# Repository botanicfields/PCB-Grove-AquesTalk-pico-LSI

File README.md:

# PCB-Grove-AquesTalk-pico-LSI
# AquesTalk pico LSI用Grove(M5)接続基板
AquesTalk pico LSI into the Grove of M5

# 1. 概要
　「AquesTalk pico LSI用Grove(M5)接続基板」は、市販の音声合成専用LSI「AquesTalk pico LSI」（別売）をGroveコネクタでM5シリーズに接続するための基板です。  
　AquesTalk pico LSIの詳細は、データシートを参照ください。
- [Data Sheet: 音声合成 LSI 「AquesTalk pico LSI」ATP3011](https://www.a-quest.com/archive/manual/atp3011_datasheet.pdf)
- [Data Sheet: 音声合成 LSI 「AquesTalk pico LSI」ATP3012](https://www.a-quest.com/archive/manual/atp3012_datasheet.pdf)

### 基板V03 の変更点
　2022年10月から基板V03を提供しています。ピンソケットJ7を追加しました。

### 委託販売
（スイッチサイエンス扱い）[AquesTalk pico LSI用Grove(M5)接続基板](https://www.switch-science.com/catalog/7625/)

### 動作例
- (YouTube）[AquesTalk pico LSI into the Grove of M5](https://youtu.be/mju6NteZsHU)  
M5AtomにI2Cで接続しています。以下のサンプルプログラムを使用しています。  
[GitHub: botanicfields/PCB-Grove-AquesTalk-pico-LSI/tree/main/BF-035_Wire](https://github.com/botanicfields/PCB-Grove-AquesTalk-pico-LSI/tree/main/BF-035_Wire)
- (YouTube）[般若心経 by AquesTalk pico LSI and M5Stack, Glove PCB, I2C](https://youtu.be/BDH4y0ca8p8)  
M5SrackにI2Cで接続しています。基板V03のJ7とM5StackのGPIO35をジャンパワイヤーで接続しています。以下のサンプルプログラムを使用しています。  
[GitHub: botanicfields/PCB-MBUS-AquesTalk-pico-LSI/tree/main/BF-034_han-nya](https://github.com/botanicfields/PCB-MBUS-AquesTalk-pico-LSI/tree/main/BF-034_han-nya)

### 組み立て例
　AquesTalk piso LSI（28ピンDIPタイプ）1個をICソケットに装着します。ATP3011用とATP3012用のソケットがあります。どちらか一方のみを装着してください。  
AquestTalk pico LSIの取り付け: 左 ATP3011, 右 ATP3012  

## 1.1 特徴
- AquesTalk pico LSI（28ピンDIPタイプ）1個を搭載できます。
- ATP3011, ATP3012の両方に対応しています。
- パワーアンプ（LM4871）を内蔵し、スピーカーを直接駆動できます。
- M5シリーズのGrove仕様に合わせ、電源+5V、信号3.3Vに対応します。
- AquestTalk pico LSIは3.3Vで動作し、M5シリーズに直結できます。
- DIPスイッチで動作モード・通信モードを設定できます。
- 動作モード・通信モードの変更を反映するリセットボタンがあります。
- I2C接続用、UART接続用のGroveコネクタがあり、接続方法を選べます。
- スタンドアロンモードのためのコネクタがあります。
- SPI接続も可能です（ハンダ付けが必要です）。

DIP: Dual In-line Package  
I2C: Inte-Integrated Circuit  
UART: Universal Asynchronous Receiver Transmitter  
SPI: Serial Peripheral Interface

## 1.2 内容物
- AquesTalk pico LSI用Grove(M5)接続基板（完成品）1枚  
- Groveケーブル20cm 1本（M5Stack純正品）  
- 説明書 1部  

※ AquesTalk pico LSIは付属しません。  
※ スピーカー、スピーカーケーブルは付属しません。  
※ ケースや足などは付属しません。

### 商品写真（基板V03）
写真: 内容物、基板裏面  

## 1.3 別途必要なもの
- AquesTalk pico LSI（秋月電子通商扱い）  
[音声合成ＬＳＩ　ＡＴＰ３０１１Ｆ１－ＰＵ（ゆっくりな女性の音声）
ATP3011F1-PU](https://akizukidenshi.com/catalog/g/gI-06220/)  
[音声合成ＬＳＩ　ＡＴＰ３０１１Ｆ４－ＰＵ（かわいい女性の音声）
ATP3011F4-PU](https://akizukidenshi.com/catalog/g/gI-05665/)  
[音声合成ＬＳＩ　ＡＴＰ３０１１Ｍ６－ＰＵ（男性の音声）
ATP3011M6-PU](https://akizukidenshi.com/catalog/g/gI-06225/)  
[音声合成ＬＳＩ　ＡＴＰ３０１２Ｆ６－ＰＵ（女性の音声明瞭版）
ATP3012F6-PU](https://akizukidenshi.com/catalog/g/gI-09973/)  
[音声合成ＬＳＩ　ＡＴＰ３０１２Ｒ５－ＰＵ（小型ロボットの音声）
ATP3012R5-PU](https://akizukidenshi.com/catalog/g/gI-11517/)  
- スピーカー、スピーカーケーブル  
4～8Ω程度、1W以上が望ましいです
- 工具  
ドライバ（ターミナルブロックの締め付けに必要です）など
- M5Stack, M5Atom  
サンプルプログラムは、M5Stack Core Basic, M5Atomで動作を確認しています
- Arduino-IDEが動作する環境  
サンプルプログラムは、Arduino IDE用です
- その他  
SLEEP信号などを接続する場合には、ジャンパワイヤー等が必要です。SPI接続の場合には、ピンヘッダおよびハンダ付けが必要です

# 2. 接続

## 2.1 I2C接続
　SCL, SDAの表記のあるGroveコネクタJ5に接続します。基板上にプルアップ抵抗はありません。M5シリーズ側でのプルアップを使用します。

### (1)M5AtomのGroveコネクタに接続  
　I2Cとして、SCL=GPIO32, SDA=GPIO26を指定します。サンプルプログラムではWire1を選択します。

### (2)「M5Atom用GROVEコネクタ基板※（別売）」経由で接続  
　I2Cとして、デフォルトのWire（SCL=GPIO21, SDA=GPIO25）を使用できます。  
※（スイッチサイエンス扱い）[M5Atom用GROVEコネクタ基板](https://www.switch-science.com/catalog/7309/)

### (3)M5StackのGroveコネクタに接続  
　I2Cとして、デフォルトのWire（SCL=GPIO22, SDA=GPIO21）を使用できます。

## 2.2 UART接続
　TX, RXの表記のあるGroveコネクタJ4に接続します。基板上のTXがM5シリーズのRXに、基板上のRXがM5シリーズのTXに接続されます。

### (1)M5AtomのGroveコネクタに接続  
　M5Atom側は、RX=GPIO32, TX=GPIO26を指定します。

### (2)M5StackのGPIOに接続  
　接続には、「GROVE - 4ピン - ジャンパオスケーブル※（別売）」相当のケーブルが必要です。M5Stack側は、RX=GPIO16, TX=GPIO17, +5V, GND を接続します。  
※（スイッチサイエンス扱い）[GROVE - 4ピン - ジャンパオスケーブル](https://www.switch-science.com/catalog/6245/)

## 2.3 SPI接続
　SS, +5V, GNDは、ピンソケットJ3に接続します。SCK, MOSI, MISOは、J1(ICSP)に接続します。ICSPのピンヘッダは実装していません。ピンヘッダを別途手配いただき、基板へハンダ付けしてください。接続にはジャンパワイヤー等が必要です。
- SPI: Serial Periphral Interface
- SCK: Serial ClocK
- MOSI: Master Out Slave In
- MISO: Master In Slave Out
- SS: Slave Select
- GND: Ground
- ICSP: In Circuit Serial Programming

### M5StackのGPIOに接続
　接続にはジャンパワイヤー等が必要です。SCK=GPIO18, MISO=GPIO19, MOSI=GPIO23, SS=GPIO5, +5V, GND を接続します。

## 2.4 スタンドアロン
　J2に「ダイオードマトリクススイッチ16基板※」を接続し、ボタン操作で15種類の音声を再生できます。以下の写真でM5Stackは、電源として使用しています。  
※（スイッチサイエンス扱い）[ダイオードマトリクススイッチ16基板](https://www.switch-science.com/catalog/7626/)

## 2.5 その他共通
### J3 SLEEP信号
　AquesTalk pico LSIのSLEEPピンをGPIOに接続できます。SLEEP=LowでAquesTalk pico LSIがスリープ状態になります。ATP3011のUART接続において9600bpsより速い速度が必要な場合、「セーフモード」ではなく「コマンド入力モード」が必要であり、速度設定のためにSLEEPの接続が必要です。

### J3 PLAY信号
　AquesTalk pico LSIのPLAYピンをGPIOに接続できます。AquesTalk pico LSIが音声再生中の間、PLAY=Lowとなります。

### J6 スピーカー
　スピーカーを接続します。2本のいずれもGNDではありません。

### J7 音声信号（基板V03）
　音量調節ボリュームに入る時点のアナログ音声をジャンパワイヤー等に取り出すことができます。ATP3011、ATP3012でピンが異なります。  
ATP3011の例  
  
ATP3012の例  

# 3. 設定（DIPスイッチ）
　動作モードおよび使用するインタフェース（通信モード）に合わせて、基板上のDIPスイッチを設定します。おすすめはI2C接続です。DIPスイッチの設定はリセット時に反映されます。**DIPスイッチの設定を変更後、基板上のリセットボタンを押す必要があります**。出荷時の設定は、セーフモード・I2C接続・パワーアンプが常に動作状態（OFF,ON,OFF,ON,ON）です。

| 1 | 2 | 3 | 4 | 5 |動作モード|通信モード|備考|
|:-:|:-:|:-:|:-:|:-:|:-:|:-:|:- |
|OFF|OFF|OFF|ON | - | コマンド入力モード |I2C |I2CアドレスはEEPROMに設定した値（初期値0x2E）|
|OFF|ON |OFF|ON | - | セーフモード |I2C |I2Cアドレスは強制的に0x2E|
|OFF|OFF|OFF|OFF| - | コマンド入力モード |UART|設定されたスピードで動作 (*1) |
|OFF|ON |OFF|OFF| - | セーフモード |UART|強制的に9600bpsで動作|
|OFF| - |ON |OFF| - | - | SPI mode 3 | - |
|OFF| - |ON |ON | - | - | SPI mode 0 |サンプルプログラムはSPI mode 0で動作|
|ON |OFF| - | - | - | スタンドアロンモード | - |PC0-3の信号入力によりプリセットメッセージを選択して再生|
|ON |ON | - | - | - | デモモード | - |プリセットメッセージを順番に自動再生|
| - | - | - | - |ON | - | - |パワーアンプが常に動作状態 |
| - | - | - | - |OFF| - | - |音声再生中以外は、パワーアンプをシャットダウンする(*2)|

※ 1, 2, 3, 4, 5は、DIPスイッチの番号です。DIPスイッチはONでGND接続のため、ON=0, OFF=1です。  
(*1) ATP3011の場合、SLEEP解除後の'?'送信で自動設定します。ATP3012の場合EEPROMに設定します。  
(*2) 音声再生の前後にノイズが発生します。

# 4. サンプルプログラム
　AquesTalk pico LSIをM5StackまたはM5Atomに接続し、I2C(Wire), UART(Serial), SPIで動作させるプログラムです。デモの内容は同じです。Arduino-IDE環境で使用します。基板の接続や設定を予め使用するインタフェースに合わせておく必要があります。

### BF-035_Wireフォルダ
　AqeusTalk pico LSIをI2Cで動作させるサンプルプログラムです。#defineでM5Stack, M5Atomのいずれかを選択します。

### BF-035_Serialフォルダ
　AqeusTalk pico LSIをUARTで動作させるサンプルプログラムです。#defineでM5Stack, M5Atomのいずれかを選択します。

### BF-035_Spiフォルダ
　AqeusTalk pico LSIを SPIで動作させるサンプルプログラムです。M5Stack専用です。

## 4.1 ボタン操作 .. loop()
　ボタンを押すと、ソースコードのpreset_msgを発声します。初期値はpreset_msg[0]です。

| M5 | ボタン | 停止中 | 発声中 |
|:-:|:-:|:-:|:-:|
|M5Stack| A   | 1つ前のpreset_msgを発声 | 発声を中断して1つ前のpreset_msgを発声 |
|M5Stack| B   | 現在のpreset_msgを発声 | 発声を中断して停止 |
|M5Stack| C   | 1つ後のpreset_msgから連続して発声 | 発声を中断して1つ後のpreset_msgから連続して発生 |
|M5Atom | Btn | 現在のpreset_msgから連続して発声 | 発声を中断して停止 |

## 4.2 setup()
- SLEEPピンをHighにする（デフォルト: 実行しない）  
　AquesTalk pico LSIのSLEEPピンとが接続したGPIO5をHIGHにしてSLEEPでない状態にします。

- UARTスピードを設定（ATP3011が対象。UARTのみ。デフォルト: 実行しない）  
　AquesTalk pico LSI (ATP3011) のUARTスピードを設定します。GPIO5がAquesTalk pico LSIのSLEEPピンと接続している必要があります。

- UARTスピードを書き換え（ATP3012が対象。UARTのみ。デフォルト: 実行しない）  
　AquesTalk pico LSI (ATP3012) のUARTスピードを書き換えます。

- I2Cアドレスを書き換え（I2Cのみ。デフォルト: 実行しない）  
　AquesTalk pico LSIのI2Cアドレスを書き換えます。

- プリセットメッセージを書き込む（デフォルト: 実行しない）  
　AquesTalk pico LSIにプリセットメッセージとして、ソースコード内のpreset_msgデータを書き込みます。時間がかかります。

- EEPROMデータをダンプ（デフォルト: 実行しない）  
　AquesTalk pico LSIのEEPROMデータをシリアルモニタに表示します。時間がかかります。

- AquesTalk pico LSIのバージョンをシリアルモニタに表示

- チャイムJを発声

- チャイムKを発声

# 5. ライブラリ
　AquesTalk pico LSIを使用するためのライブラリです。

## 5.1 BF_AquesTalkPico.h
　I2C, UART, SPI共通の基本クラスです。接続するインタフェースに依ってI2C(Wire), UART(Serial), SPIのいずれかの派生クラスを使用する必要があります。

### (1) virtual int Send(const char* msg) = 0
　AquesTalk pico LSIに文字列msgを送信します。送信の様子をシリアルモニタに出力します。純粋仮想関数として定義し、使用するインタフェースに合わせて派生クラスで実装します。

### (2) virtual size_t Recv(char* res, size_t res_size) = 0
　AquesTalk pico LSIから文字列を受信します。受信完了は、'>'または'*'で判断します。純粋仮想関数として定義し、使用するインタフェースに合わせて派生クラスで実装します。

### (3) virtual bool Busy() = 0
　発声中などAquesTalk pico LSIが処理中の場合trueを応答します。falseの場合発声が終了したと判断できます。純粋仮想関数として定義し、使用するインタフェースに合わせて派生クラスで実装します。I2C, SPIではおのずとポーリングができますが、UARTではSend()による明示的なポーリングが必要です。

### (4) int ShowRes(int res_length_to_show = 1)
　AquesTalk pico LSIからの応答をシリアルモニタに出力します。res_length_to_showに2を渡すと、応答が1文字以下の場合にシリアルモニタへの出力を抑止できます。I2C、SPIのポーリングによる応答が正常（'>', 1文字）の場合のシリアルモニタへの出力を省略できます。

### (5) int DumpEeprom()
　AquesTalk pico LSIのEEPROM (アドレス0x000-0x3FF) の値をシリアルモニタに出力します。

### (6) int WriteEeprom(int address, int data)
　AquesTalk pico LSIのEEPROMにデータを書き込みます。

### (7) int WritePresetMsg(const char* msg[], int num_of_msg)
　AquesTalk pico LSIのEEPROMにプリセットメッセージを書き込みます。書き込みの様子をシリアルモニタに出力します。

### (8)  int WriteSpeed(int speed)
　発話速度をEEPROMに設定します。50～300を設定できます。デフォルトは100です。

### (9)  int WritePause(int pause)
　文末ポーズの長さをEEPROMに設定します。256～65535を設定できます。65535を設定すると自動になります。デフォルトは65535です。

### (10) int WriteSerialSpeed(int serial_speed)
　AquesTalk pico LSI (ATP3012) のシリアル通信速度を書き換えます。デフォルトは9600です。

### (11) int WriteI2cAddress(int i2c_address)
　AquesTalk pico LSIのI2Cアドレスを書き換えます。デフォルトは0x2Eです。

## 5.2 BF_AquesTalkPicoWire.h
　AquesTalk pico LSIとI2Cでインタフェースする派生クラスです。

### int Begin(TwoWire &wire, int i2c_address = 0x2e);
　AquesTalk pico LSIを接続するI2CとI2Cアドレスを指定します。

## 5.3 BF_AquesTalkPicoSerial.h
　AquesTalk pico LSIとUARTでインタフェースする派生クラスです。

### int Begin(Stream &stream);
　AquesTalk pico LSIを接続するUARTを指定します。

## 5.4 BF_AquesTalkPicoSpi.h
　AquesTalk pico LSIとSPIでインタフェースする派生クラスです。

### int Begin(SPIClass &spi, int ss);
　AquesTalk pico LSIを接続するSPIとSSとして使用するGPIOを指定します。

# 6. 参考
Qiita: [AquesTalk pico LSI を M5Stack の I2C, UART, SPI で動かす](https://qiita.com/BotanicFields/items/fff644f408c291e5a5f0)

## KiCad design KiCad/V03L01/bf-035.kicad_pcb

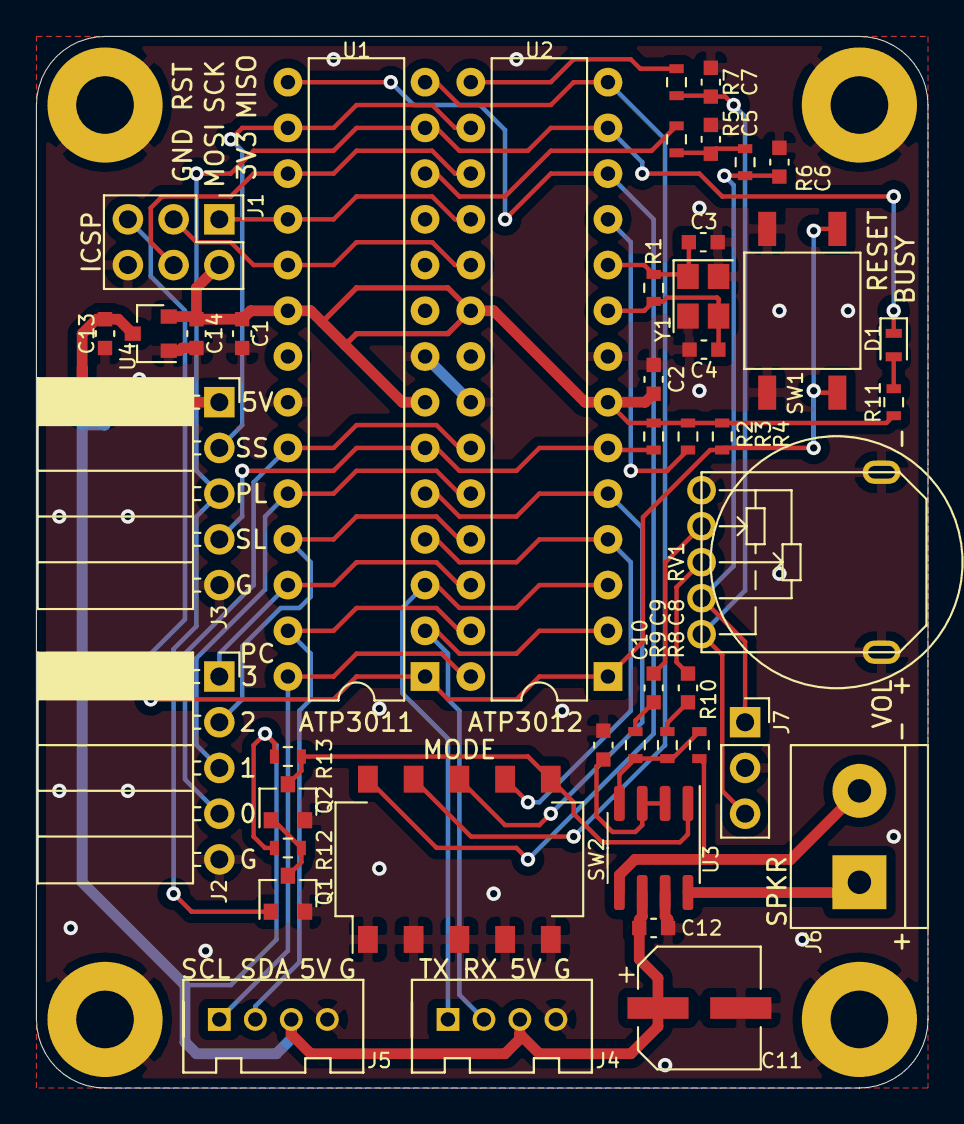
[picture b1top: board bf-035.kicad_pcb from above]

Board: 2 copper layers, 49.5 x 58.4 mm, 45 parts (0 on the bottom side), 41 nets.

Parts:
C1, C2, C5, C12: 100n; BF@C_0603_1608Metric
C3, C4: 10p; BF@C_0603_1608Metric
C6: 22n; BF@C_0603_1608Metric
C7: 10n; BF@C_0603_1608Metric
C8, C9: 33n; BF@C_0603_1608Metric
C10, C13, C14: 1u; BF@C_0603_1608Metric
C11: 100u; BF@CP_Elec_6.3x5.3
D1: BUSY; BF@LED_0603_1608Metric
J1: ICSP; PinHeader_2x03_P2.54mm_Vertical
J2: PRESET; PinSocket_1x05_P2.54mm_Horizontal
J3: CONTROL; PinSocket_1x05_P2.54mm_Horizontal
J4: Grove UART; HW4-2.0
J5: Grove I2C; HW4-2.0
J6: SPKR; BF@TerminalBlock_2_P5.08mm_d1.3mm
J7: AOUT; PinSocket_1x03_P2.54mm_Vertical
Q1, Q2: DTC143Z; SOT-23
R1: 1M; BF@R_0603_1608Metric
R2, R3, R4, R12, R13: 10k; BF@R_0603_1608Metric
R5: 470; BF@R_0603_1608Metric
R6, R11: 2.2k; BF@R_0603_1608Metric
R7: 3.3k; BF@R_0603_1608Metric
R8, R9: 22k; BF@R_0603_1608Metric
R10: 68k; BF@R_0603_1608Metric
RV1: 10kA; BF@RK10J
SW1: SW_Push; BF@K2-6639SP
SW2: MODE; SW_DIP_SPSTx05_Slide_Omron_A6S-510x_W8.9mm_P2.54mm
U1: ATP3011; DIP-28_W7.62mm
U2: ATP3012; DIP-28_W7.62mm
U3: LM4871; SOIC-8_3.9x4.9mm_P1.27mm
U4: XC6206P332MR; SOT-23
Y1: 16MHz; Crystal_SMD_3225-4Pin_3.2x2.5mm

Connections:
+3V3: C1.1, C2.1, C14.1, J1.2, R2.2, R3.2, R4.2, R11.1, U1.7, U1.20, U2.7, U2.20, U4.2
+5V: C11.1, C12.1, C13.1, J3.1, J4.3, J5.3, R12.1, R13.1, U3.6, U4.3
/AOUT_3011: R5.2, U1.12
/AOUT_3012: R7.2, U2.15
/CLK16: R3.1, U2.11
/MISO: J1.1, U1.18, U2.18
/MOSI: J1.4, U1.17, U2.17
/PC0: J2.4, U1.23, U2.23
/PC1: J2.3, U1.24, U2.24
/PC2: J2.2, U1.25, U2.25
/PC3: J2.1, U1.26, U2.26
/PMOD0: SW2.9, U1.14, U2.14
/PMOD1: SW2.10, U1.15, U2.12
/RXD: J4.2, U1.2, U2.2
/SCK: J1.3, U1.19, U2.19
/SCL: J5.1, U1.28, U2.28
/SD: Q2.3, R13.2, SW2.6, U3.1
/SDA: J5.2, U1.27, U2.27
/SMOD0: SW2.7, U1.4, U2.4
/SMOD1: SW2.8, U1.5, U2.5
/TXD: J4.1, U1.3, U2.3
/~PLAY: D1.1, J3.3, Q1.1, U1.13, U2.13
/~RESET: J1.5, R4.1, SW1.1, U1.1, U2.1
/~SLEEP: J3.4, R2.1, U1.6, U2.6
/~SS: J3.2, U1.16, U2.16
GND: C1.2, C2.2, C3.2, C4.2, C5.1, C6.1, C7.1, C10.1, C11.2, C12.2, C13.2, C14.2, J1.6, J2.5, J3.5, J4.4, J5.4, J7.2, Q1.2, Q2.2, RV1.1, RV1.6, SW1.2, SW2.1, SW2.2, SW2.3, SW2.4, SW2.5, U1.8, U1.22, U2.8, U2.22, U3.7, U4.1, Y1.2, Y1.4
unnamed: C3.1, R1.2, U2.10, Y1.1
unnamed: C4.1, R1.1, U2.9, Y1.3
unnamed: C5.2, R5.1, R6.2
unnamed: C6.2, J7.1, R6.1, RV1.4
unnamed: C7.2, J7.3, R7.1, RV1.5
unnamed: C8.1, R8.2
unnamed: C8.2, RV1.3
unnamed: C9.1, R9.2
unnamed: C9.2, RV1.2
unnamed: C10.2, U3.2, U3.3
unnamed: D1.2, R11.2
unnamed: J6.1, U3.8
unnamed: J6.2, R10.1, U3.5
unnamed: Q1.3, Q2.1, R12.2
unnamed: R8.1, R9.1, R10.2, U3.4

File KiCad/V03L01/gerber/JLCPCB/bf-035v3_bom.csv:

Comment,Designator,Footprint,LCSC
1u,"C10,C13,C14",bf:BF@C_0603_1608Metric,C15849
100u,C11,bf:BF@CP_Elec_6.3x5.3,C267461
100n,"C1,C2,C5,C12",bf:BF@C_0603_1608Metric,C14663
10p,"C3,C4",bf:BF@C_0603_1608Metric,C1634
22n,C6,bf:BF@C_0603_1608Metric,C21122
10n,C7,bf:BF@C_0603_1608Metric,C57112
33n,"C8,C9",bf:BF@C_0603_1608Metric,C21117
BUSY,D1,bf:BF@LED_0603_1608Metric,C72038
ICSP,J1,Connector_PinHeader_2.54mm:PinHeader_2x03_P2.54mm_Vertical,
PRESET,J2,Connector_PinSocket_2.54mm:PinSocket_1x05_P2.54mm_Horizontal,
CONTROL,J3,Connector_PinSocket_2.54mm:PinSocket_1x05_P2.54mm_Horizontal,
Grove UART,J4,OPL_Connector:HW4-2.0,
Grove I2C,J5,OPL_Connector:HW4-2.0,
SPKR,J6,bf:BF@TerminalBlock_2_P5.08mm_d1.3mm,
AOUT,J7,Connector_PinSocket_2.54mm:PinSocket_1x03_P2.54mm_Vertical,
DTC143Z,"Q1,Q2",Package_TO_SOT_SMD:SOT-23,C15236
1M,R1,bf:BF@R_0603_1608Metric,C22935
68k,R10,bf:BF@R_0603_1608Metric,C23231
2.2k,"R6,R11",bf:BF@R_0603_1608Metric,C4190
10k,"R2,R3,R4,R12,R13",bf:BF@R_0603_1608Metric,C25804
470,R5,bf:BF@R_0603_1608Metric,C23179
3.3k,R7,bf:BF@R_0603_1608Metric,C22978
22k,"R8,R9",bf:BF@R_0603_1608Metric,C31850
10kA,RV1,bf:BF@RK10J,
SW_Push,SW1,bf:BF@K2-6639SP,C879344
MODE,SW2,Button_Switch_SMD:SW_DIP_SPSTx05_Slide_Omron_A6S-510x_W8.9mm_P2.54mm,C54951
ATP3011,U1,Package_DIP:DIP-28_W7.62mm,
ATP3012,U2,Package_DIP:DIP-28_W7.62mm,
LM4871,U3,Package_SO:SOIC-8_3.9x4.9mm_P1.27mm,C7554
XC6206P332MR,U4,Package_TO_SOT_SMD:SOT-23,C5446
16MHz,Y1,Crystal:Crystal_SMD_3225-4Pin_3.2x2.5mm,C13738

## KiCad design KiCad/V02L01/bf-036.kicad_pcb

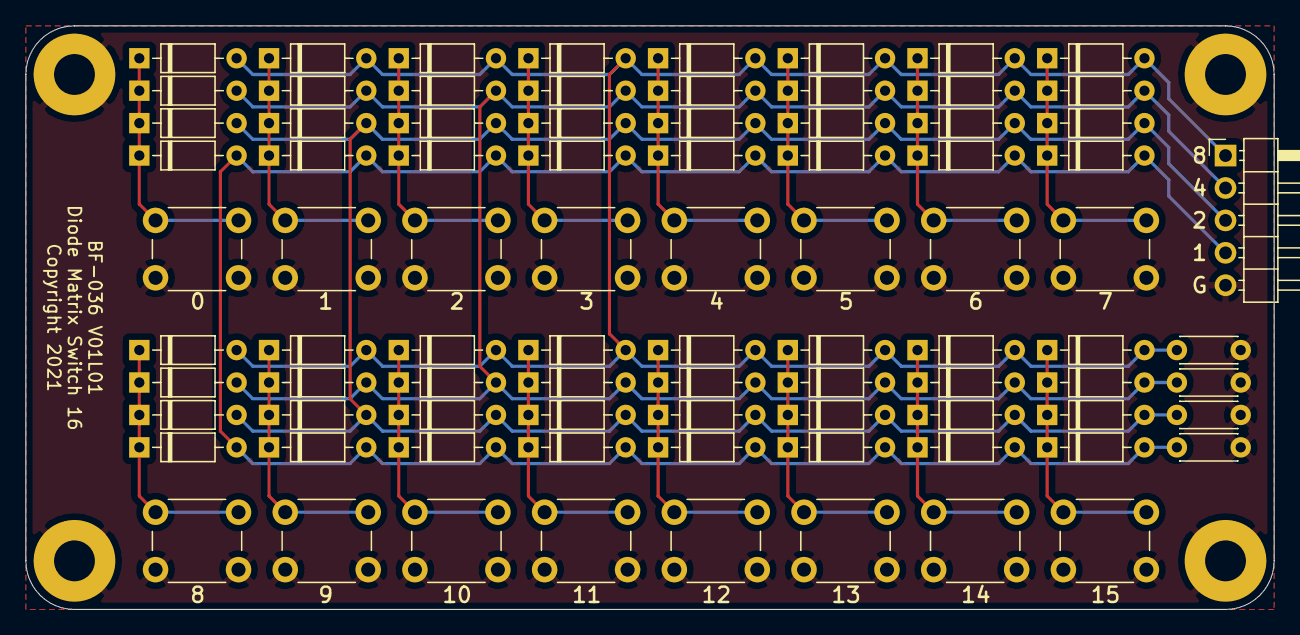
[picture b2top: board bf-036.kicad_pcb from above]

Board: 2 copper layers, 97.8 x 45.7 mm, 85 parts (0 on the bottom side), 21 nets.

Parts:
C1, C2, C3, C4: 10n; C_Disc_D4.3mm_W1.9mm_P5.00mm
D1, D2, D3, D4, D5, D6, D7, D8, D9, D10, D11, D12, D13, D14, D15, D16, D17, D18, D19, D20, D21, D22, D23, D24, D25, D26, D27, D28, D29, D30, D31, D32, D33, D34, D35, D36, D37, D38, D39, D40, D41, D42, D43, D44, D45, D46, D47, D48, D49, D50, D51, D52, D53, D54, D55, D56, D57, D58, D59, D60, D61, D62, D63, D64: D; D_DO-35_SOD27_P7.62mm_Horizontal
J1: CODE; PinHeader_1x05_P2.54mm_Horizontal
SW1: 0; SW_PUSH_6mm
SW2: 1; SW_PUSH_6mm
SW3: 2; SW_PUSH_6mm
SW4: 3; SW_PUSH_6mm
SW5: 4; SW_PUSH_6mm
SW6: 5; SW_PUSH_6mm
SW7: 6; SW_PUSH_6mm
SW8: 7; SW_PUSH_6mm
SW9: 8; SW_PUSH_6mm
SW10: 9; SW_PUSH_6mm
SW11: 10; SW_PUSH_6mm
SW12: 11; SW_PUSH_6mm
SW13: 12; SW_PUSH_6mm
SW14: 13; SW_PUSH_6mm
SW15: 14; SW_PUSH_6mm
SW16: 15; SW_PUSH_6mm

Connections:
GND: C1.2, C2.2, C3.2, C4.2, J1.5, SW1.2, SW2.2, SW3.2, SW4.2, SW5.2, SW6.2, SW7.2, SW8.2, SW9.2, SW10.2, SW11.2, SW12.2, SW13.2, SW14.2, SW15.2, SW16.2
unnamed: C1.1, D1.2, D5.2, D9.2, D13.2, D17.2, D21.2, D25.2, D29.2, D33.2, D37.2, D41.2, D45.2, D49.2, D53.2, D57.2, D61.2, J1.1
unnamed: C2.1, D2.2, D6.2, D10.2, D14.2, D18.2, D22.2, D26.2, D30.2, D34.2, D38.2, D42.2, D46.2, D50.2, D54.2, D58.2, D62.2, J1.2
unnamed: C3.1, D3.2, D7.2, D11.2, D15.2, D19.2, D23.2, D27.2, D31.2, D35.2, D39.2, D43.2, D47.2, D51.2, D55.2, D59.2, D63.2, J1.3
unnamed: C4.1, D4.2, D8.2, D12.2, D16.2, D20.2, D24.2, D28.2, D32.2, D36.2, D40.2, D44.2, D48.2, D52.2, D56.2, D60.2, D64.2, J1.4
unnamed: D1.1, D2.1, D3.1, D4.1, SW1.1
unnamed: D5.1, D6.1, D7.1, D8.1, SW2.1
unnamed: D9.1, D10.1, D11.1, D12.1, SW3.1
unnamed: D13.1, D14.1, D15.1, D16.1, SW4.1
unnamed: D17.1, D18.1, D19.1, D20.1, SW5.1
unnamed: D21.1, D22.1, D23.1, D24.1, SW6.1
unnamed: D25.1, D26.1, D27.1, D28.1, SW7.1
unnamed: D29.1, D30.1, D31.1, D32.1, SW8.1
unnamed: D33.1, D34.1, D35.1, D36.1, SW9.1
unnamed: D37.1, D38.1, D39.1, D40.1, SW10.1
unnamed: D41.1, D42.1, D43.1, D44.1, SW11.1
unnamed: D45.1, D46.1, D47.1, D48.1, SW12.1
unnamed: D49.1, D50.1, D51.1, D52.1, SW13.1
unnamed: D53.1, D54.1, D55.1, D56.1, SW14.1
unnamed: D57.1, D58.1, D59.1, D60.1, SW15.1
unnamed: D61.1, D62.1, D63.1, D64.1, SW16.1

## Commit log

2021-11-23 examples
2021-11-27 DOC
    add document for product
2021-12-18 examples
    add unsigned related to millis()
2022-08-22 Busy() added
    Busy() added and button operations are improved
2022-08-22 Update README.md
    some typos
2022-08-22 BF-035_xx.ino
    typos
2022-09-24 BF_AquesTalkPico.cpp
    add WriteSpeed(), WritePause()
2022-09-25 typos
    update README.md, etc.
2022-10-01 PCB V03
    add PCB V03

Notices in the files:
KiCad/V02L01/bf-036.kicad_pcb:
Copyright 2021 BotanicFields, Inc.
